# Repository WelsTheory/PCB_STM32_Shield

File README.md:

# Nucleo-STM32-Shield
Shield Pensado para la Nucleo 144 - Exactamente la NUCLEO F429ZI

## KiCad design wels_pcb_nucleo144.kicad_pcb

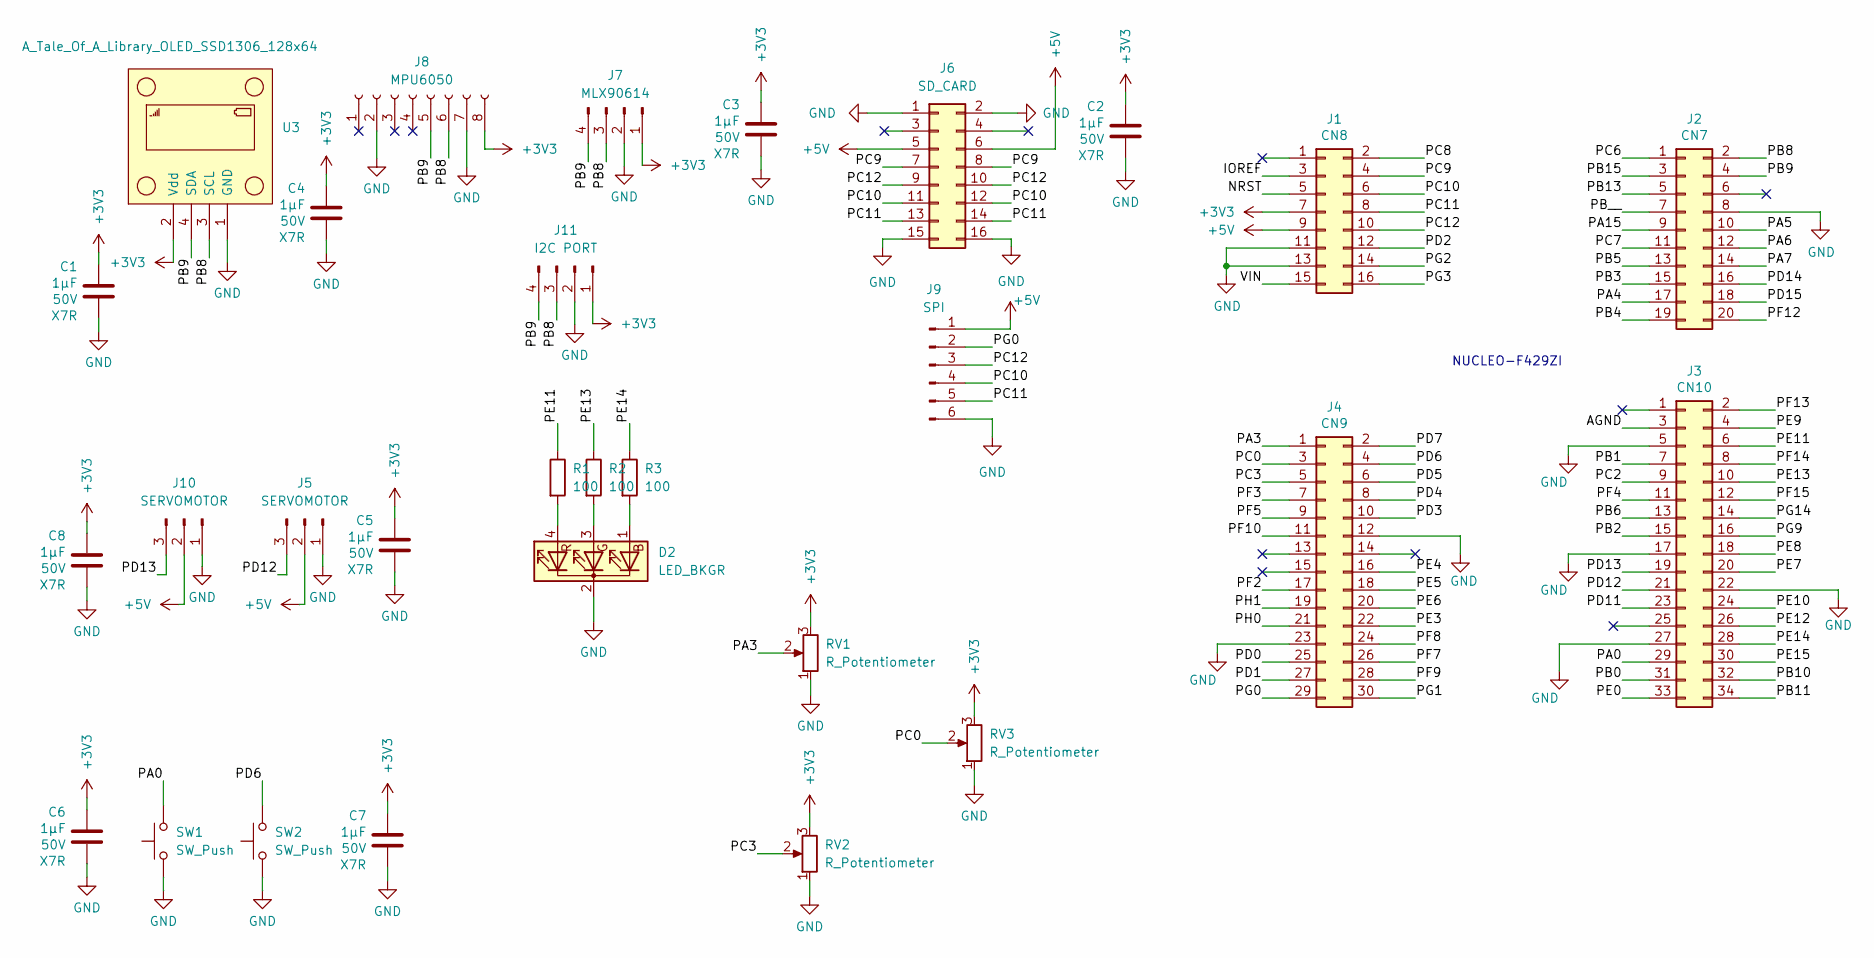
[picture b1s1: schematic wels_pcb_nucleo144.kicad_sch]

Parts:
C1, C2, C3, C4, C5, C6, C7, C8: 1μF; C_0805_2012Metric; Voltage 50V; JLCPCB Basic Part
D2: LED_BKGR; LED_D5.0mm-4_RGB_Wide_Pins
J1: CN8; PinSocket_2x08_P2.54mm_Vertical; JLCPCB do not place
J2: CN7; PinSocket_2x10_P2.54mm_Vertical; JLCPCB do not place
J3: CN10; PinSocket_2x17_P2.54mm_Vertical; JLCPCB do not place
J4: CN9; PinSocket_2x15_P2.54mm_Vertical; JLCPCB do not place
J5, J10: SERVOMOTOR; PinHeader_1x03_P2.54mm_Vertical
J6: SD_CARD; PinSocket_2x08_P2.54mm_Vertical
J7: MLX90614; PinSocket_1x04_P2.54mm_Vertical
J8: MPU6050; PinSocket_1x08_P2.54mm_Vertical
J9: SPI; PinSocket_1x06_P2.54mm_Vertical
J11: I2C PORT; PinSocket_1x04_P2.54mm_Vertical
R1, R2, R3: 100; R_0805_2012Metric
RV1, RV2, RV3: R_Potentiometer; Potentiometer_Vishay_T73XW_Horizontal
SW1, SW2: SW_Push; SW_PUSH_6mm
U3: A_Tale_Of_A_Library_OLED_SSD1306_128x64; PinHeader_1x04_P2.54mm_Vertical

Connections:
+3V3: C1.2, C2.2, C3.2, C4.2, C5.2, C6.2, C7.2, C8.2, J1.7, J7.1, J8.8, J11.1, RV1.3, RV2.3, RV3.3, U3.2 (Vdd)
+5V: J1.9, J5.2, J6.5, J6.6, J9.1, J10.2
/AGND: J3.3
/IOREF: J1.3
/NRST: J1.5
/PA0: J3.29, SW1.2
/PA3: J4.1, RV1.2
/PA4: J2.17
/PA5: J2.10
/PA6: J2.12
/PA7: J2.14
/PA15: J2.9
/PB0: J3.31
/PB1: J3.7
/PB2: J3.15
/PB3: J2.15
/PB4: J2.19
/PB5: J2.13
/PB6: J3.13
/PB8: J2.2, J7.3, J8.6, J11.3, U3.3 (SCL)
/PB9: J2.4, J7.4, J8.5, J11.4, U3.4 (SDA)
/PB10: J3.32
/PB11: J3.34
/PB13: J2.5
/PB15: J2.3
/PB__: J2.7
/PC0: J4.3, RV3.2
/PC2: J3.9
/PC3: J4.5, RV2.2
/PC6: J2.1
/PC7: J2.11
/PC8: J1.2
/PC9: J1.4, J6.7, J6.8
/PC10: J1.6, J6.11, J6.12, J9.4
/PC11: J1.8, J6.13, J6.14, J9.5
/PC12: J1.10, J6.9, J6.10, J9.3
/PD0: J4.25
/PD1: J4.27
/PD2: J1.12
/PD3: J4.10
/PD4: J4.8
/PD5: J4.6
/PD6: J4.4, SW2.2
/PD7: J4.2
/PD11: J3.23
/PD12: J3.21, J5.3
/PD13: J3.19, J10.3
/PD14: J2.16
/PD15: J2.18
/PE0: J3.33
/PE3: J4.22
/PE4: J4.16
/PE5: J4.18
/PE6: J4.20
/PE7: J3.20
/PE8: J3.18
/PE9: J3.4
/PE10: J3.24
/PE11: J3.6, R1.1
/PE12: J3.26
/PE13: J3.10, R2.1
/PE14: J3.28, R3.1
/PE15: J3.30
/PF2: J4.17
/PF3: J4.7
/PF4: J3.11
/PF5: J4.9
/PF7: J4.26
/PF8: J4.24
/PF9: J4.28
/PF10: J4.11
/PF12: J2.20
/PF13: J3.2
/PF14: J3.8
/PF15: J3.12
/PG0: J4.29, J9.2
/PG1: J4.30
/PG2: J1.14
/PG3: J1.16
/PG9: J3.16
/PG14: J3.14
/PH0: J4.21
/PH1: J4.19
/VIN: J1.15
GND: C1.1, C2.1, C3.1, C4.1, C5.1, C6.1, C7.1, C8.1, D2.2 (K), J1.11, J1.13, J2.8, J3.5, J3.17, J3.22, J3.27, J4.12, J4.23, J5.1, J6.1, J6.2, J6.15, J6.16, J7.2, J8.2, J8.7, J9.6, J10.1, J11.2, RV1.1, RV2.1, RV3.1, SW1.1, SW2.1, U3.1 (GND)
unnamed: D2.1 (BA), R3.2
unnamed: D2.3 (GA), R2.2
unnamed: D2.4 (RA), R1.2

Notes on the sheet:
NUCLEO-F429ZI

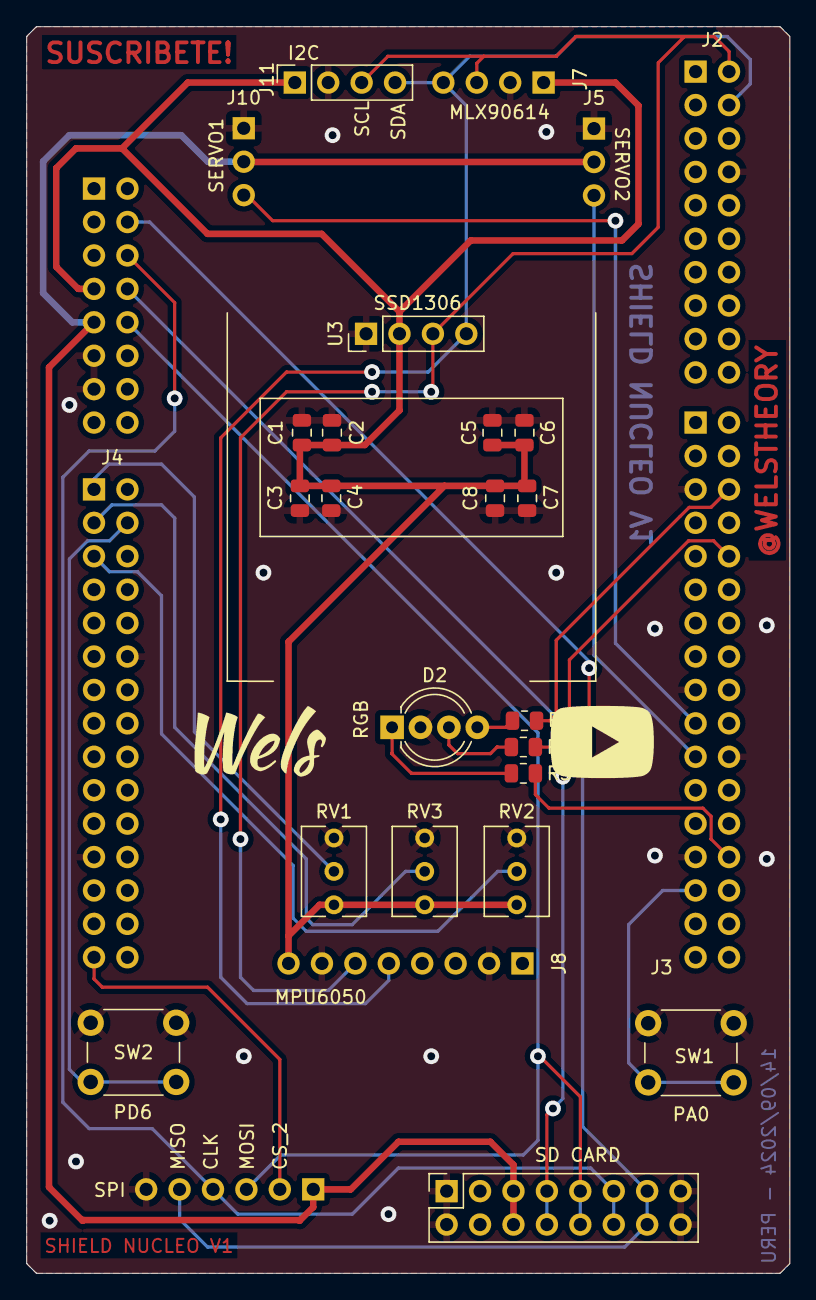
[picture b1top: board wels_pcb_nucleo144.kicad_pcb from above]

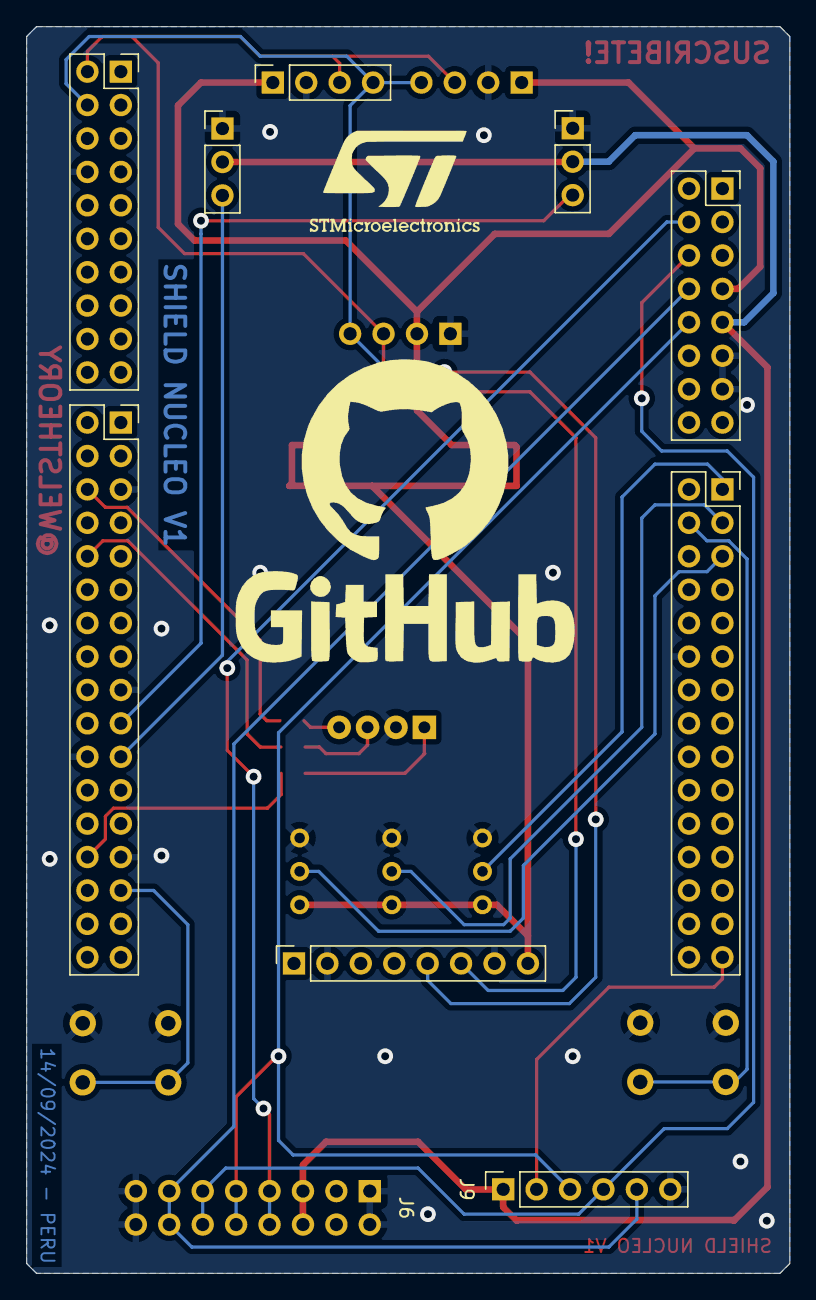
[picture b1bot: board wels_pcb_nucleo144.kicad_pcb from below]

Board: 2 copper layers, 58.0 x 94.8 mm, 29 parts (9 on the bottom side), 23 nets.

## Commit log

2024-10-28 PCB Shield STM32 V1
2025-04-08 Correccion alimentacion 5V para SD Card y cambio de footprint del LED RGB
